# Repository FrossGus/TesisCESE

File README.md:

# TesisCESE
Tesis de la Carrera de Especialización en Sistemas Embebidos de la UBA

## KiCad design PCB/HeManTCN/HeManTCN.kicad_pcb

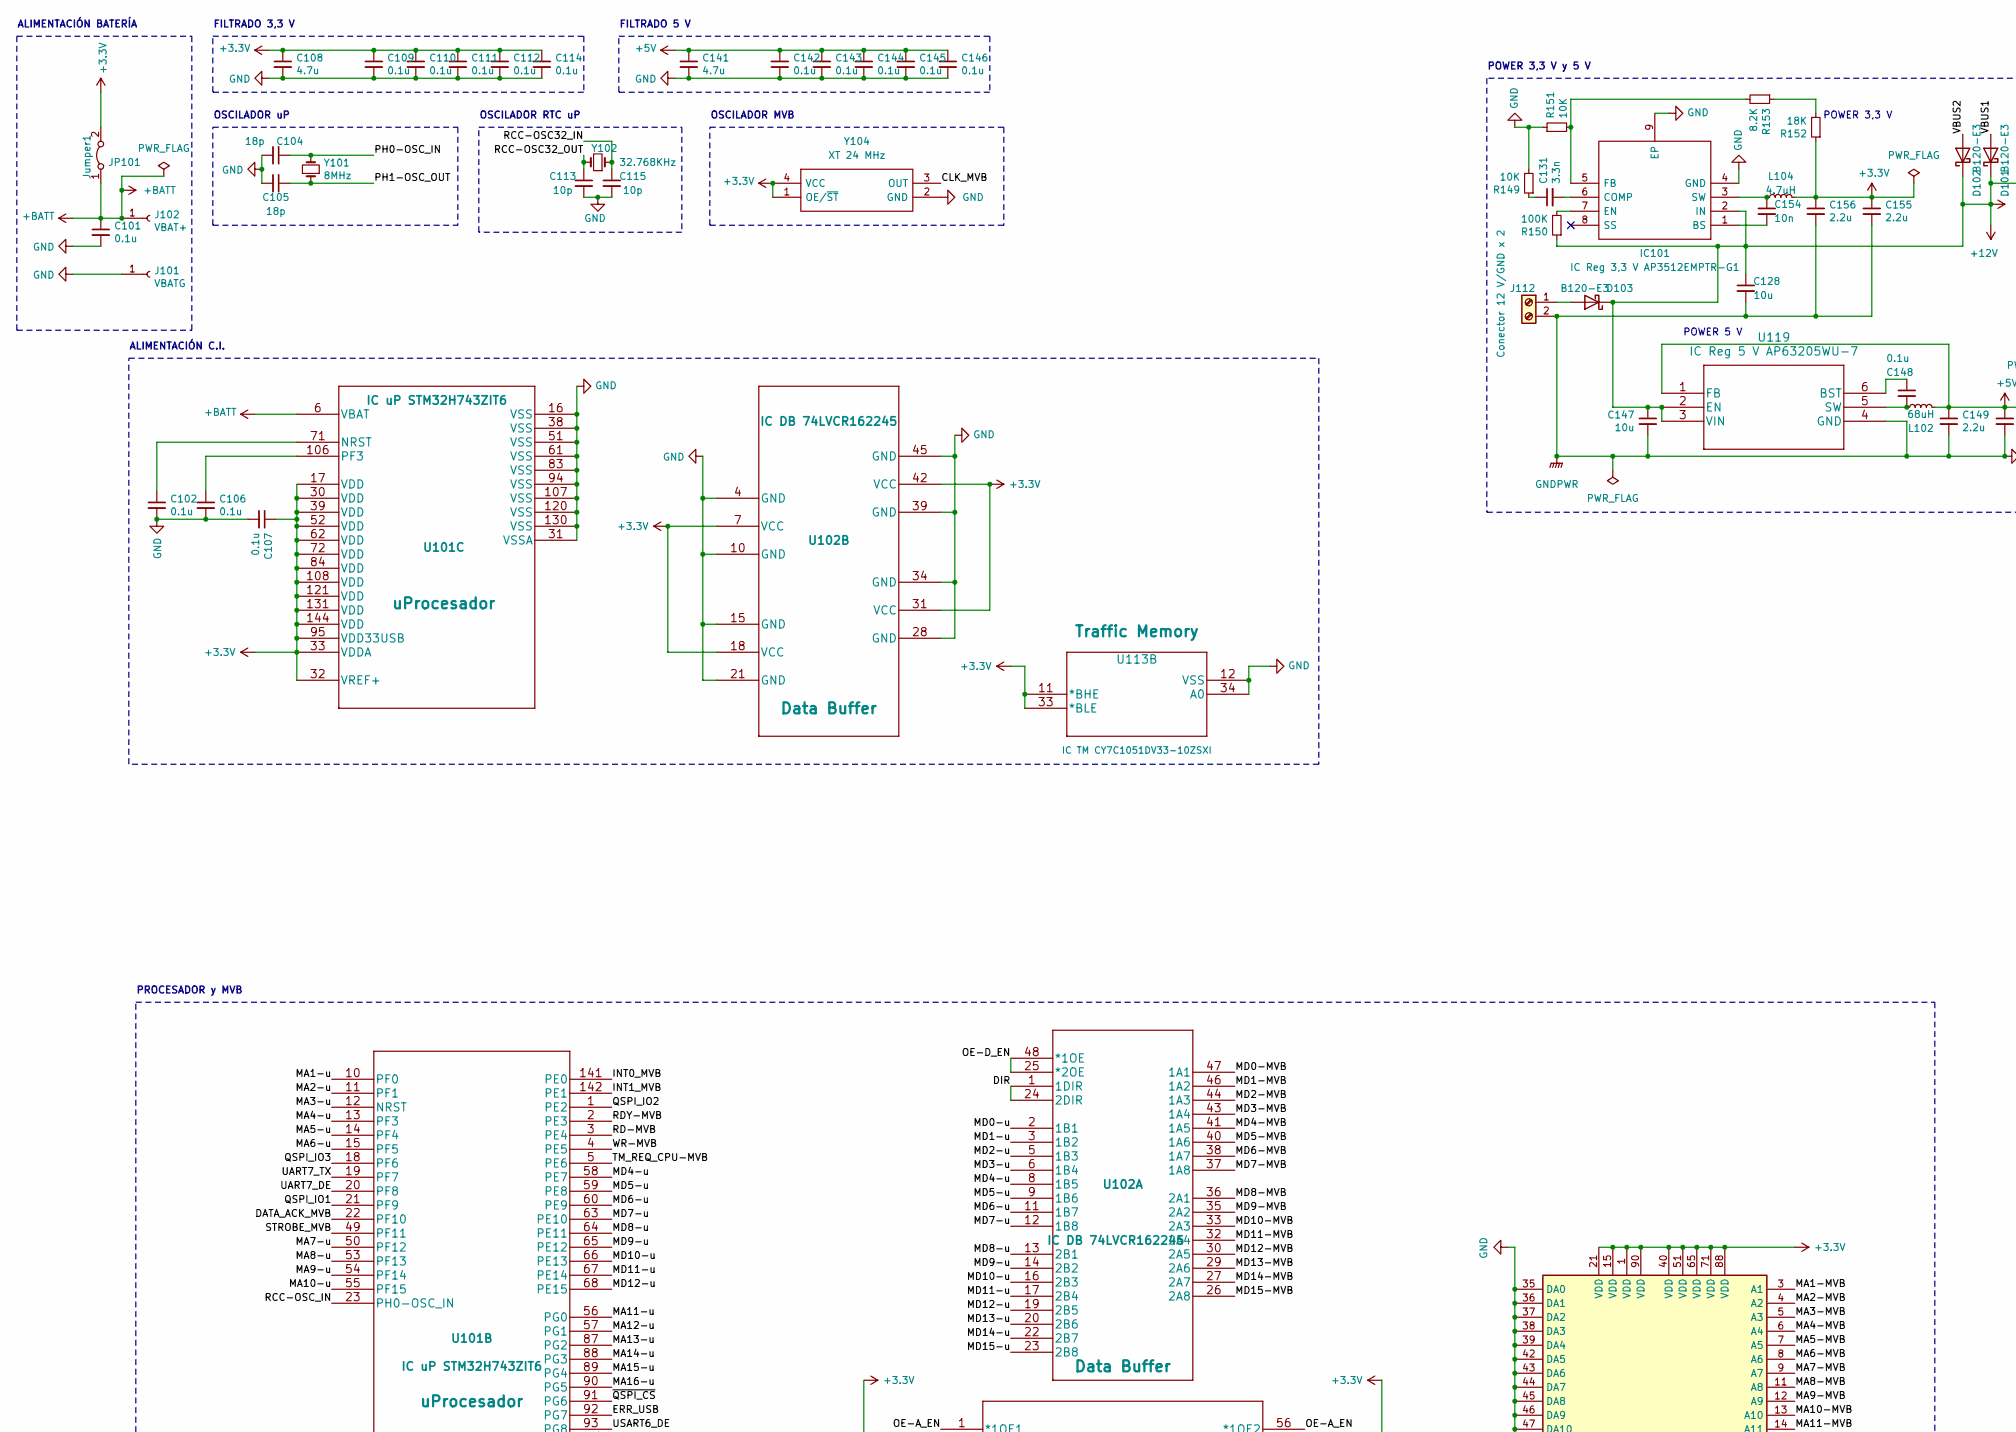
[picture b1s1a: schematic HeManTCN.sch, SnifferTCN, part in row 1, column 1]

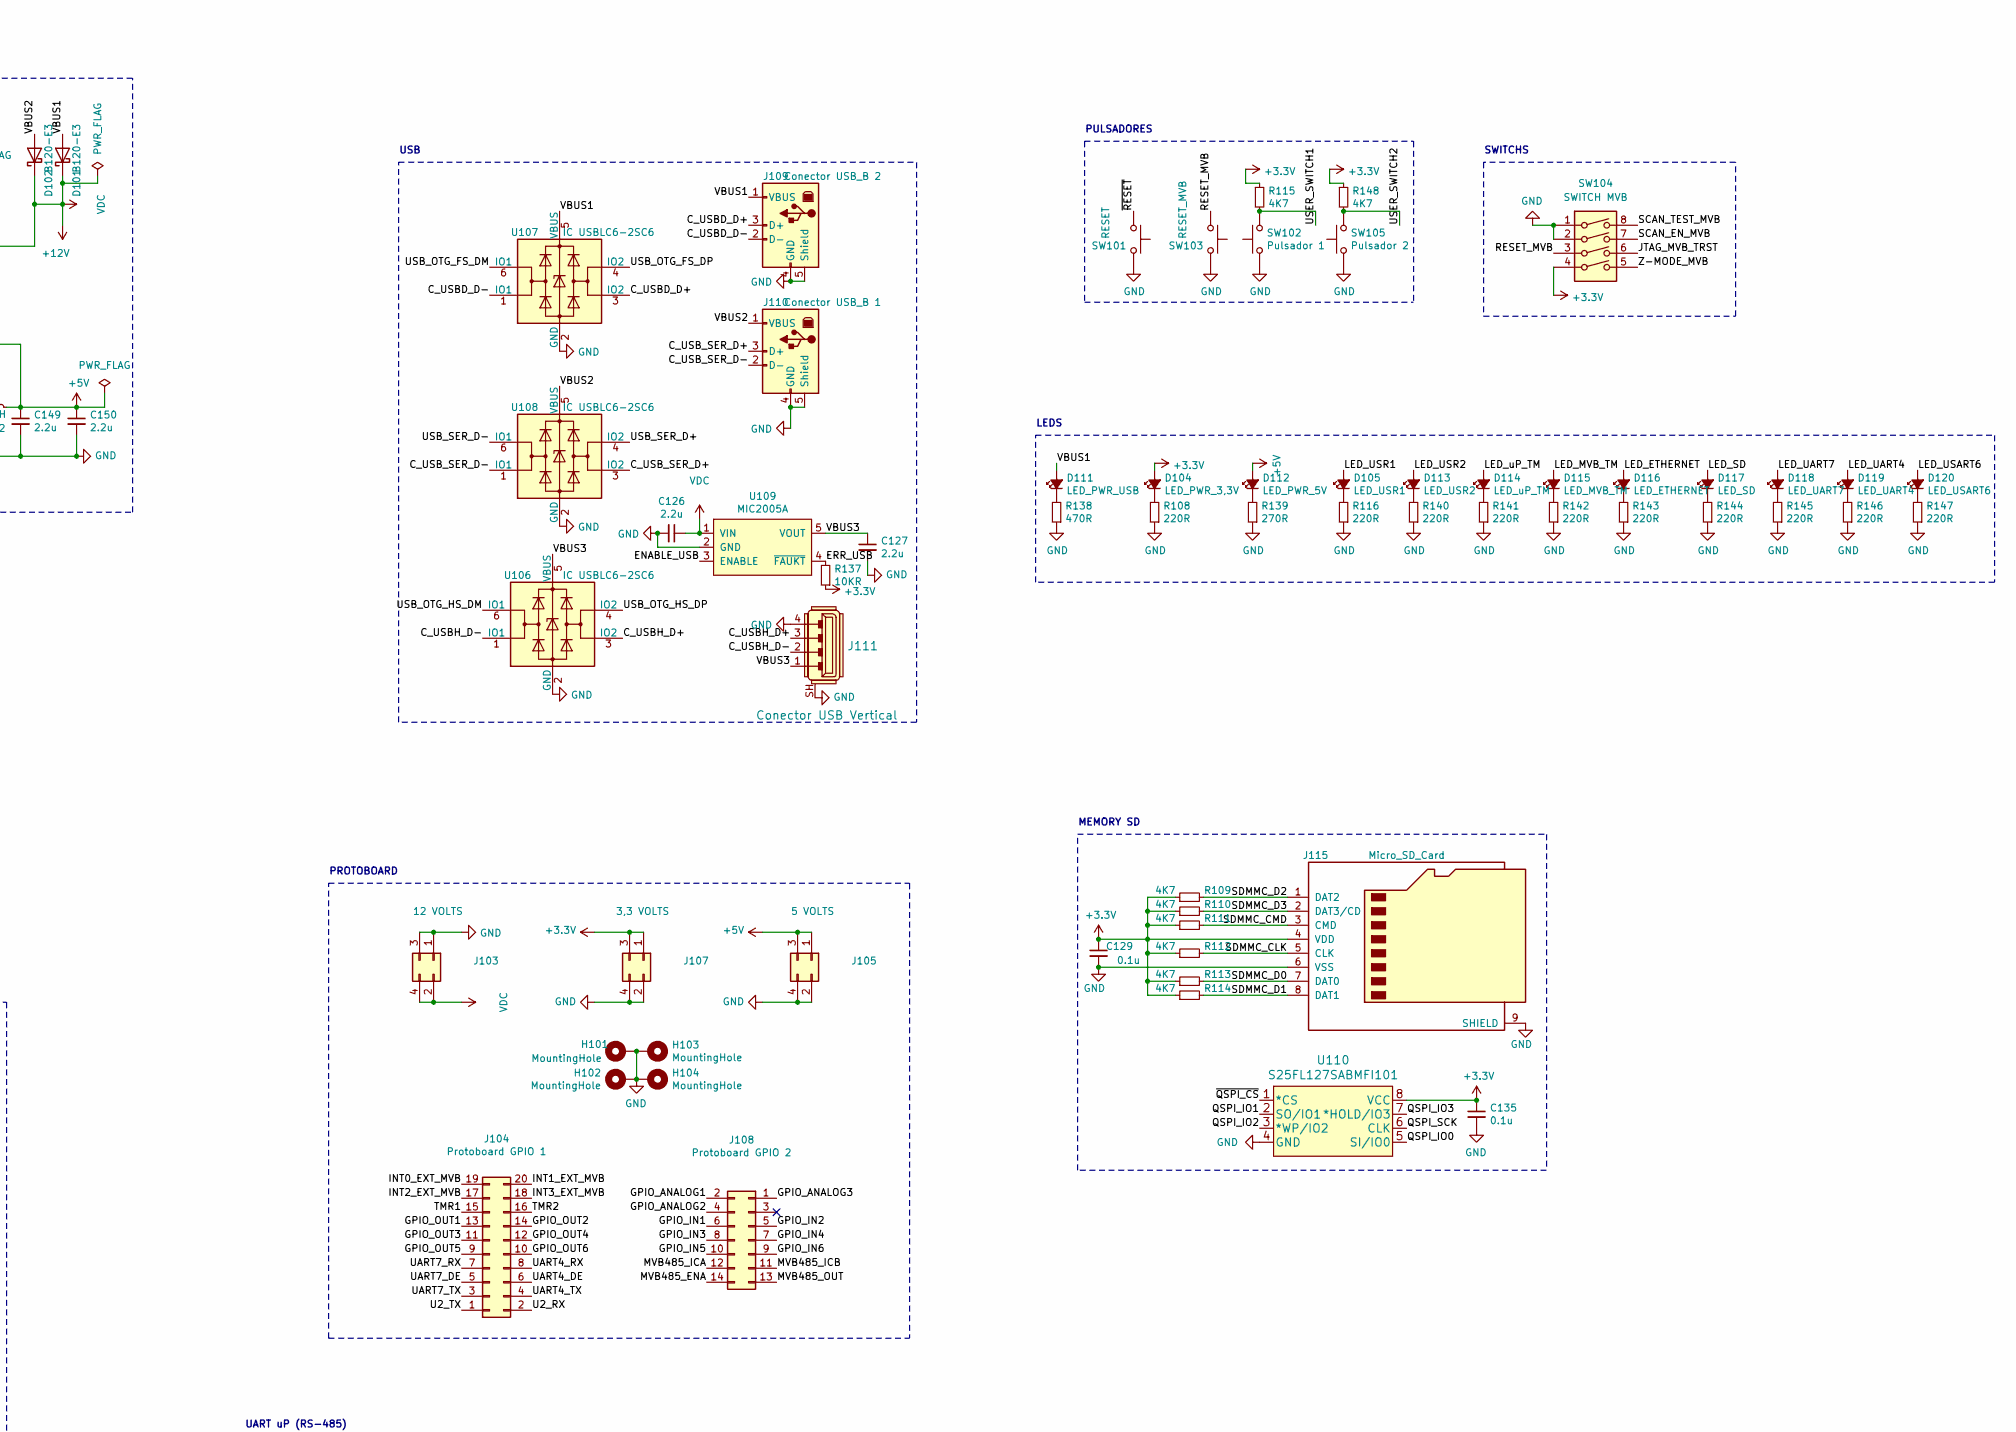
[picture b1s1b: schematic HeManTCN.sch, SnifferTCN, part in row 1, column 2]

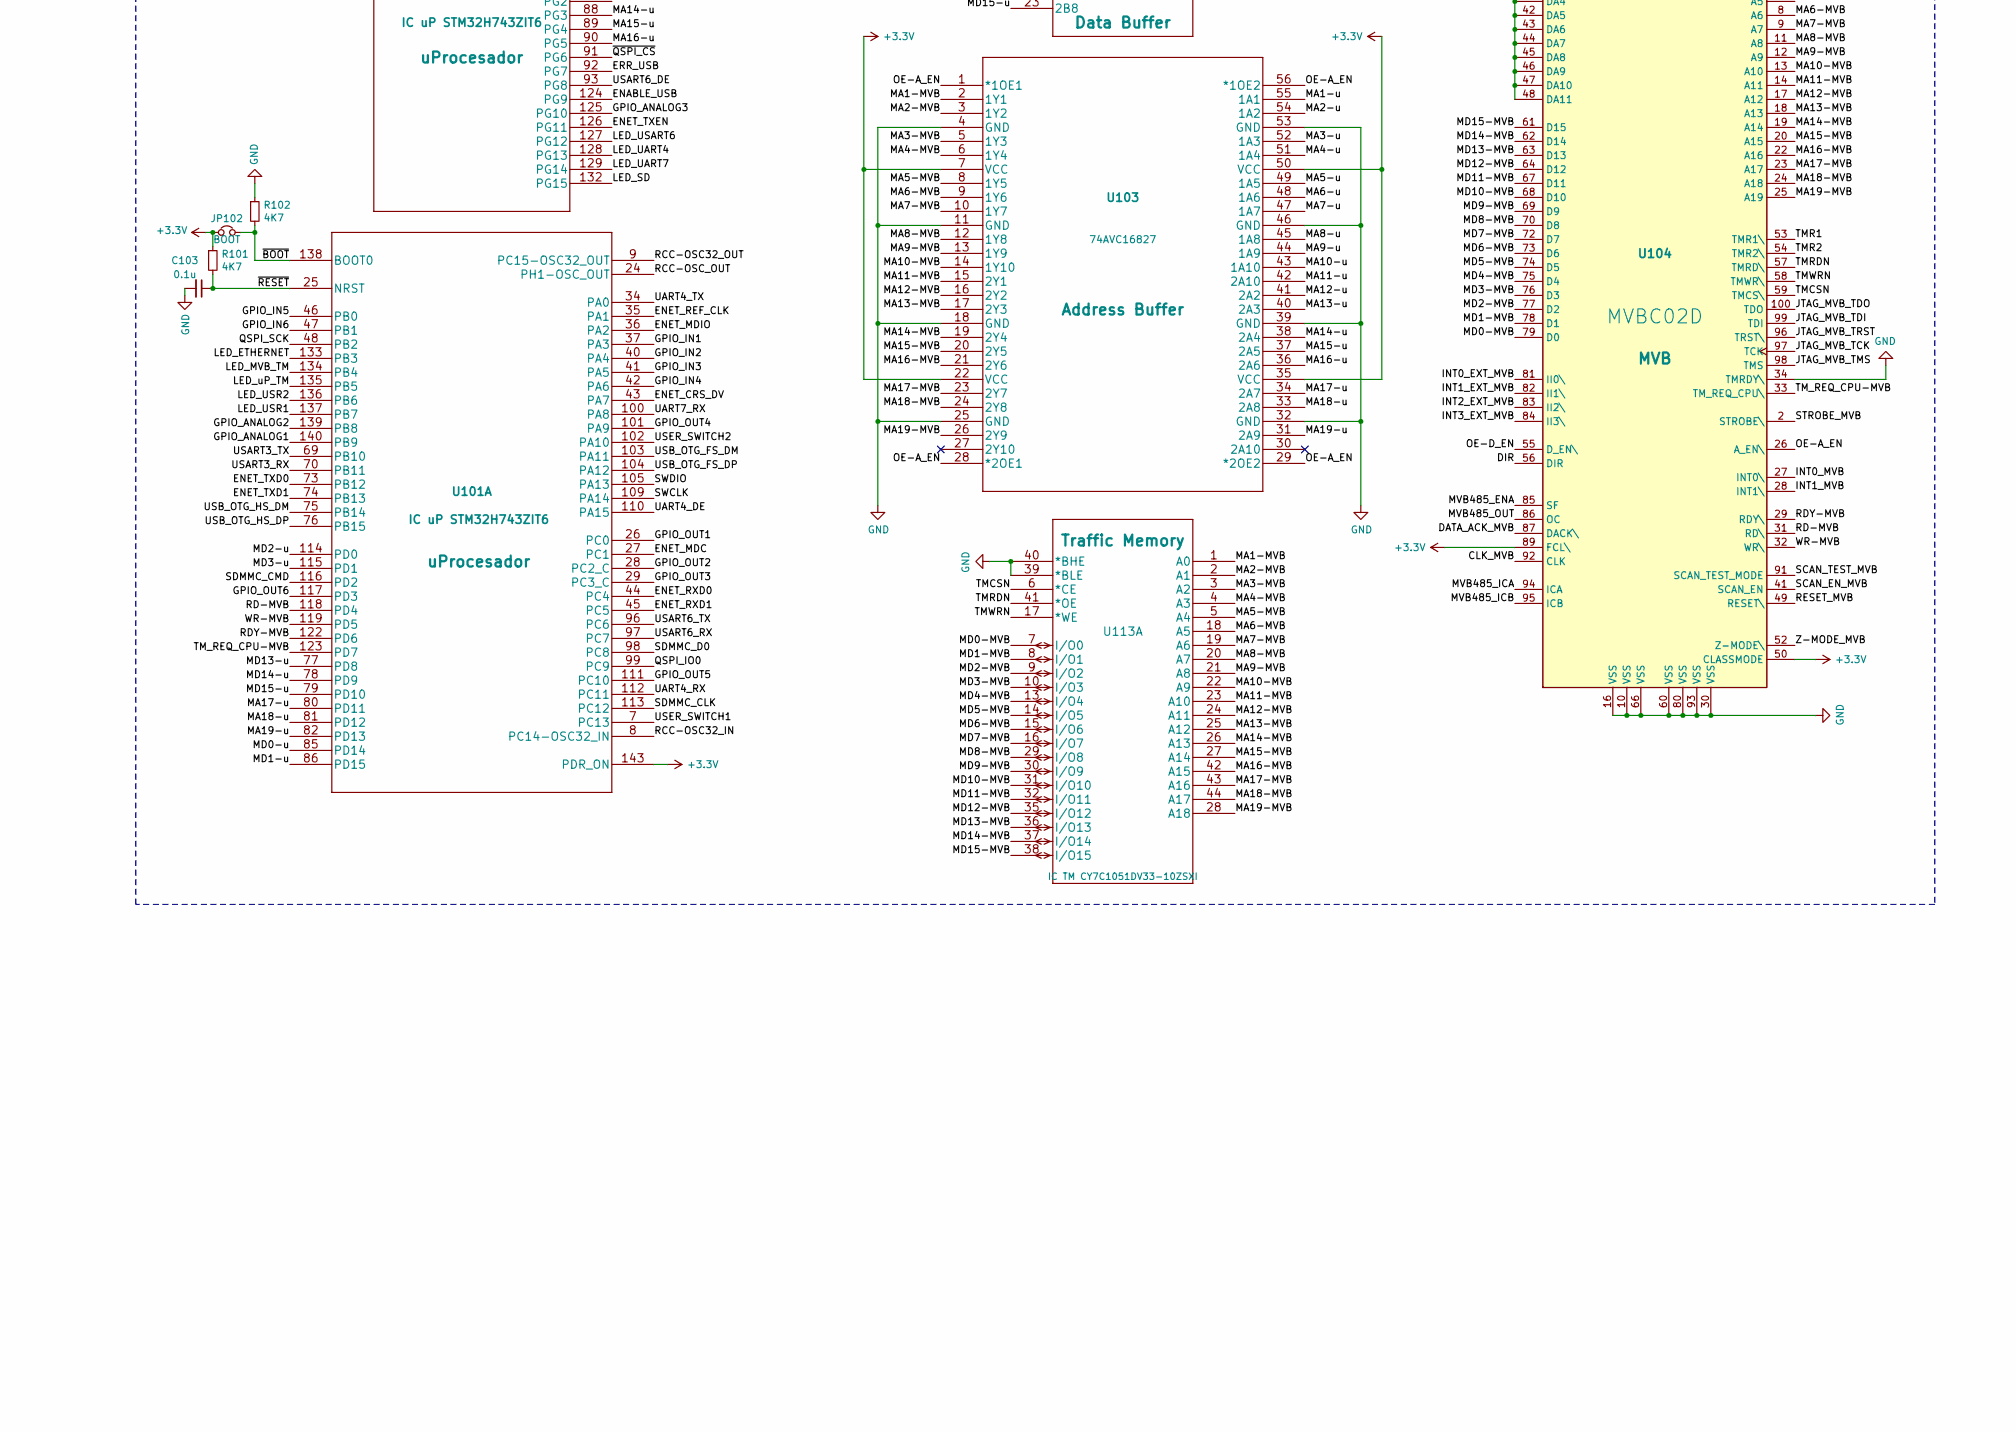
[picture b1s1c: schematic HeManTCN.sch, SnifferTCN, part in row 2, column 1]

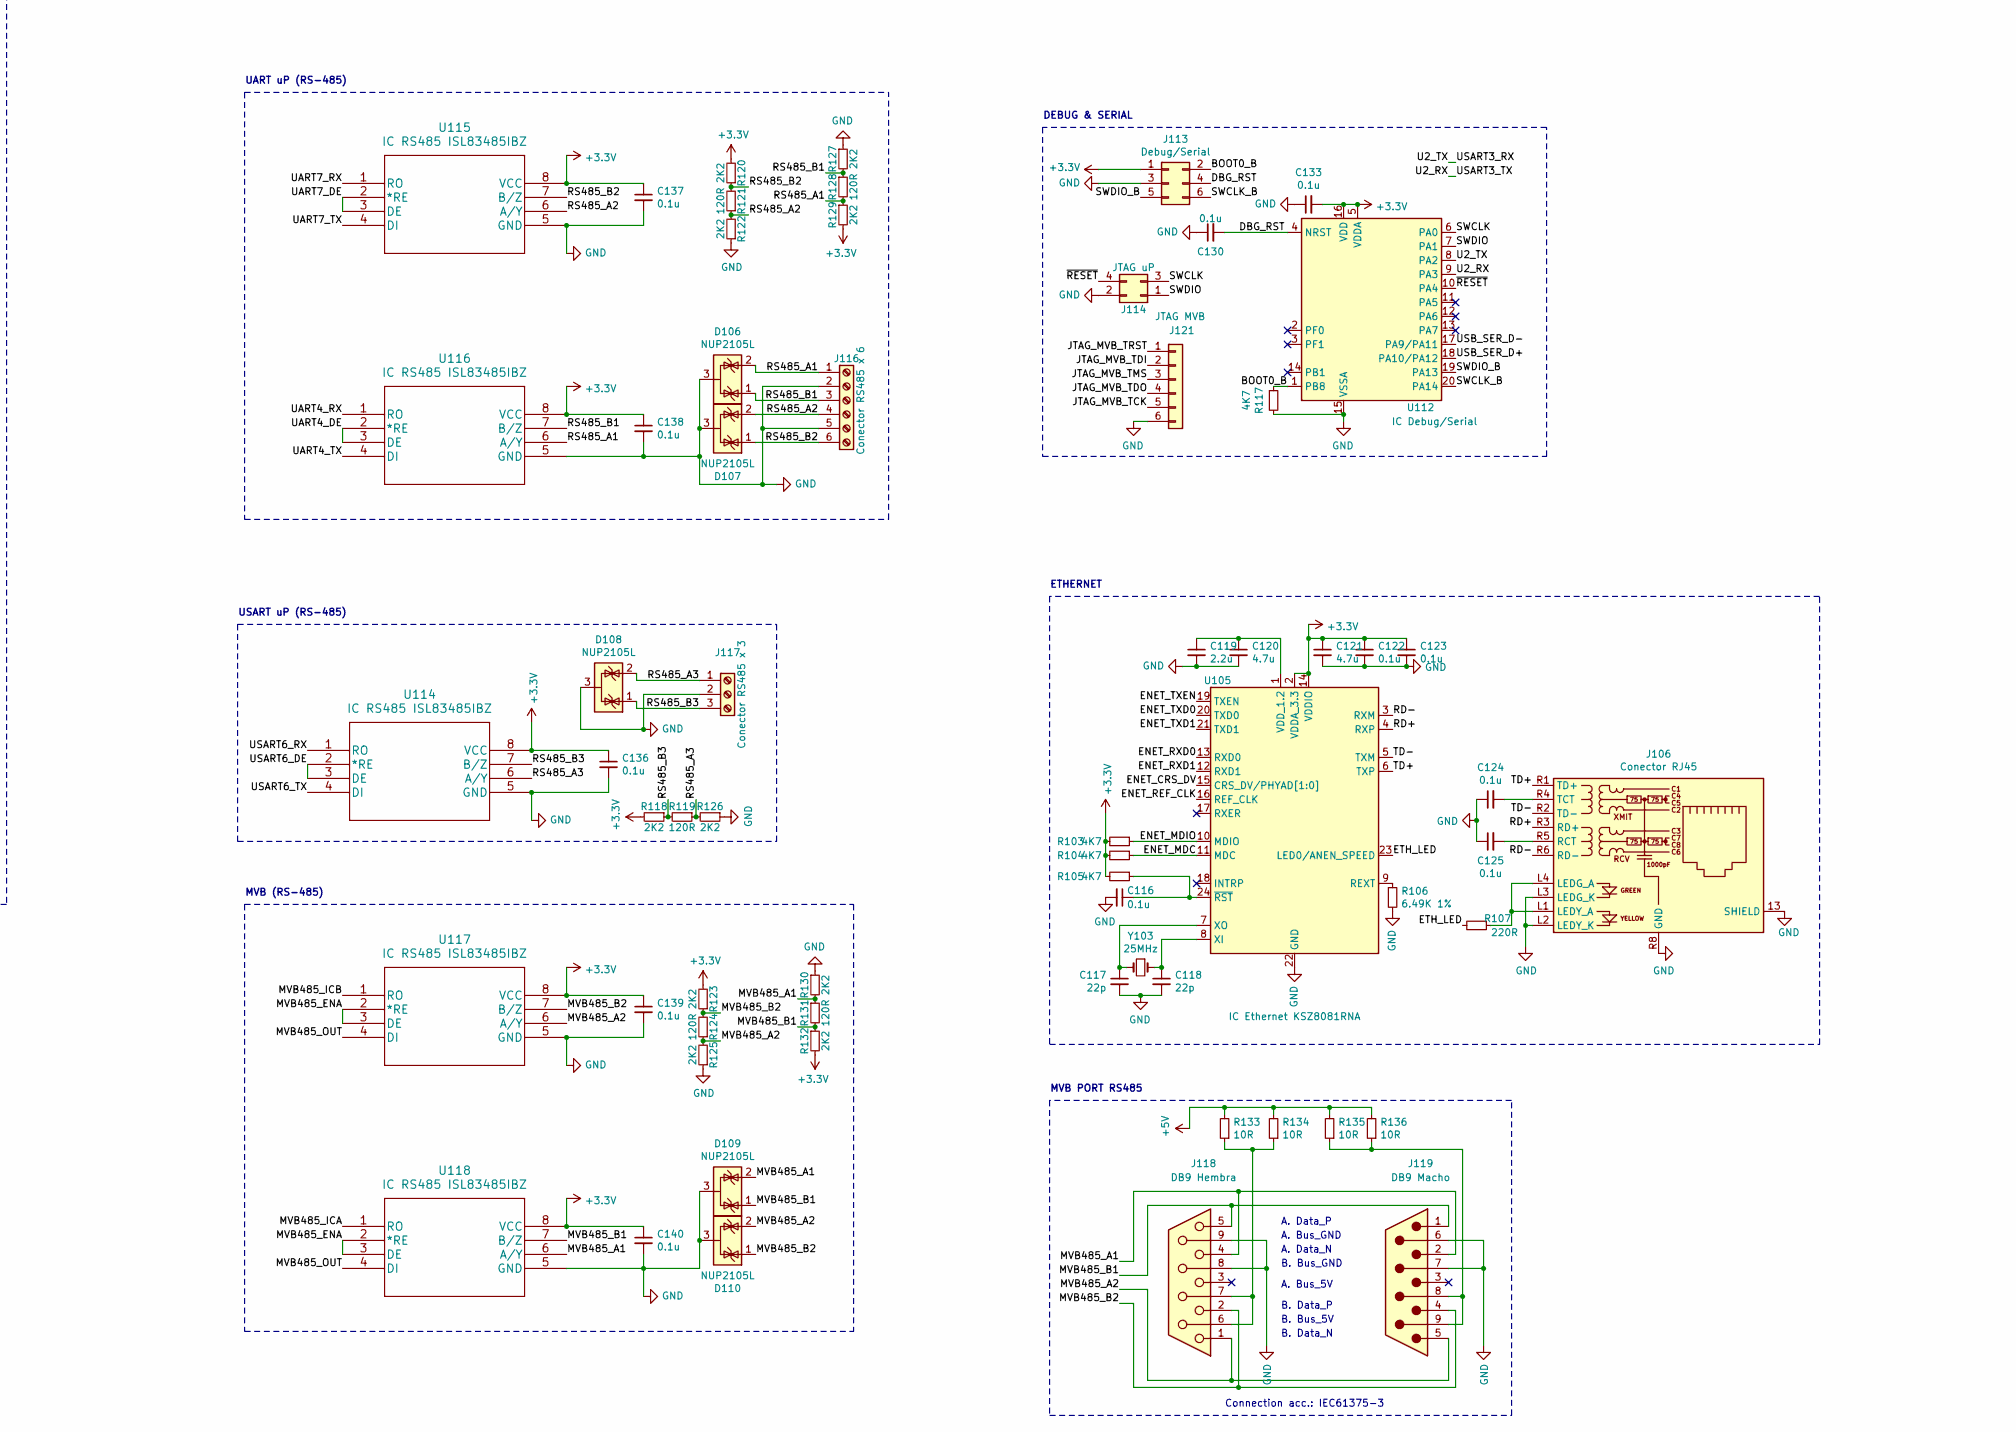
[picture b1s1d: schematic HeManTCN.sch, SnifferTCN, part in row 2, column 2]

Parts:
C101, C102, C103, C106, C107, C109, C110, C111, C112, C114, C116, C122, C123, C124, C125, C129, C130, C133, C135, C136, C137, C138, C139, C140, C142, C143, C144, C145, C146, C148: 0.1u; C_0805_2012Metric
C104, C105: 18p; C_0805_2012Metric
C108, C120, C121, C141: 4.7u; C_0805_2012Metric
C113, C115: 10p; C_0805_2012Metric
C117, C118: 22p; C_0805_2012Metric
C119, C126, C127, C149, C150, C155, C156: 2.2u; C_0805_2012Metric
C128, C147: 10u; C_0805_2012Metric
C131: 3.3n; C_0805_2012Metric
C154: 10n; C_0805_2012Metric
D101, D102, D103: B120-E3; D_SOD-123
D104: LED_PWR_3,3V; LED_0805_2012Metric_Castellated
D105: LED_USR1; LED_0805_2012Metric_Castellated
D106, D107, D108, D109, D110: NUP2105L; SOT-23
D111: LED_PWR_USB; LED_0805_2012Metric_Castellated
D112: LED_PWR_5V; LED_0805_2012Metric_Castellated
D113: LED_USR2; LED_0805_2012Metric_Castellated
D114: LED_uP_TM; LED_0805_2012Metric_Castellated
D115: LED_MVB_TM; LED_0805_2012Metric_Castellated
D116: LED_ETHERNET; LED_0805_2012Metric_Castellated
D117: LED_SD; LED_0805_2012Metric_Castellated
D118: LED_UART7; LED_0805_2012Metric_Castellated
D119: LED_UART4; LED_0805_2012Metric_Castellated
D120: LED_USART6; LED_0805_2012Metric_Castellated
H101, H102, H103, H104: MountingHole; MountingHole_3.2mm_M3_Pad_Via
IC101: IC Reg 3,3 V AP3512EMPTR-G1; AP3512EMPTR-G1; Mouser Part Number 621-AP3512EMPTR-G1
J101: VBATG; TestPoint_Loop_D1.80mm_Drill1.0mm_Beaded
J102: VBAT+; TestPoint_Loop_D1.80mm_Drill1.0mm_Beaded
J103: 12 VOLTS; PinSocket_2x05_P2.54mm_Vertical
J104: Protoboard GPIO 1; PinSocket_2x12_P2.54mm_Vertical
J105: 5 VOLTS; PinSocket_2x05_P2.54mm_Vertical
J106: Conector RJ45; RJ45_Amphenol_RJMG1BD3B8K1ANR
J107: 3,3 VOLTS; PinSocket_2x05_P2.54mm_Vertical
J108: Protoboard GPIO 2; PinSocket_2x12_P2.54mm_Vertical
J109: Conector USB_B 2; USB_B_OST_USB-B1HSxx_Horizontal
J110: Conector USB_B 1; USB_B_OST_USB-B1HSxx_Horizontal
J111: Conector USB Vertical; USB_A_Female_Vertical_RA_73725-0110BLF; MPN 73725-0110BLF; Digi-Key_PN 609-1041-ND
J112: Conector 12 V/GND x 2; Bornera2Pines_282837-2
J113: Debug/Serial; PinHeader_2x03_P2.54mm_Vertical
J114: JTAG uP; PinHeader_2x02_P2.54mm_Vertical
J115: Micro_SD_Card; microSD_HC_Hirose_DM3D-SF
J116: Conector RS485 x 6; Bornera6Pines_282837-6
J117: Conector RS485 x 3; Bornera3Pines_282837-3
J118: DB9 Hembra; DSUB-9_Female_Horizontal_P2.77x2.84mm_EdgePinOffset4.94mm_H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
J119: DB9 Macho; DSUB-9_Male_Horizontal_P2.77x2.84mm_EdgePinOffset4.94mm_Hou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
J121: JTAG MVB; PinSocket_2x05_P2.54mm_Vertical
JP101: Jumper1; PinHeader_1x02_P2.54mm_Vertical
JP102: BOOT; PinHeader_1x02_P2.54mm_Horizontal
L102: 68uH; L_6.3x6.3_H3
L104: 4.7uH; L_6.3x6.3_H3
R101, R102, R103, R104, R105, R109, R110, R111, R112, R113, R114, R115, R117, R148: 4K7; R_0805_2012Metric
R106: 6.49K 1%; R_0805_2012Metric
R107, R108, R116, R140, R141, R142, R143, R144, R145, R146, R147: 220R; R_0805_2012Metric
R118, R120, R122, R123, R125, R126, R127, R129, R130, R132: 2K2; R_0805_2012Metric
R119, R121, R124, R128, R131: 120R; R_0805_2012Metric
R133, R134, R135, R136: 10R; R_0805_2012Metric
R137: 10KR; R_0805_2012Metric
R138: 470R; R_0805_2012Metric
R139: 270R; R_0805_2012Metric
R149, R151: 10K; R_0805_2012Metric
R150: 100K; R_0805_2012Metric
R152: 18K; R_0805_2012Metric
R153: 8.2K; R_0805_2012Metric
SW101: RESET; Pulsador_TL3342F160QG
SW102: Pulsador 1; Pulsador_TL3342F160QG
SW103: RESET_MVB; Pulsador_TL3342F160QG
SW104: SWITCH MVB; Pulsador_TL3342F160QG
SW105: Pulsador 2; Pulsador_TL3342F160QG
U101: IC uP STM32H743ZIT6; LQFP-144_STM
U102: IC DB 74LVCR162245; DataBuffer SN74LVCR162245DGGR
U103: 74AVC16827; AddressBuffer SN74AVC16827DGVR
U104: MVBC02D; PQFP-100_14x20mm_P0.65mm
U105: IC Ethernet KSZ8081RNA; QFN-24-1EP_4x4mm_P0.5mm_EP2.6x2.6mm
U106, U107, U108: IC USBLC6-2SC6; SOT-23-6
U109: MIC2005A; SOT-23-5
U110: S25FL127SABMFI101
U112: IC Debug/Serial; TSSOP-20_4.4x6.5mm_P0.65mm
U113: IC TM CY7C1051DV33-10ZSXI; TSOP-44
U114, U115, U116, U117, U118: IC RS485 ISL83485IBZ; SOIC8_4X5_INR
U119: IC Reg 5 V AP63205WU-7; SOIC_05WU-7_DIO
Y101: 8MHz; Crystal_SMD_5032-2Pin_5.0x3.2mm
Y102: 32.768KHz; Crystal_SMD_MicroCrystal_CC7V-T1A-2Pin_3.2x1.5mm
Y103: 25MHz; Crystal_SMD_5032-2Pin_5.0x3.2mm
Y104: XT 24 MHz; SG7050CAN1000000MTJGA3; Mouser Part Number 732-7050CA24.0TJGA3

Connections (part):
+3V3: C107.1, C108.1, C109.1, C110.1, C111.1, C112.1, C114.1, C121.1, C122.1, C123.1, C129.1, C133.2, C135.1, C136.1, C137.1, C138.1, C139.1, C140.1, C155.1, C156.1, D104.2 (A), J107.1, J107.3, J113.1, J115.4 (VDD), JP101.2 (B), JP102.1, L104.2, R101.1, R103.2, R104.2, R105.2, R109.1, R110.1, R111.1, R112.1, R113.1, R114.1, R115.1, R118.2, R120.2, R123.2, R129.2, R132.2, R137.1, R148.1, R152.1, SW104.4, U101.17 (VDD), U101.30 (VDD), U101.32 (VREF+), U101.33 (VDDA), U101.39 (VDD), U101.52 (VDD), U101.62 (VDD), U101.72 (VDD), U101.84 (VDD), U101.95 (VDD33USB), U101.108 (VDD), U101.121 (VDD), U101.131 (VDD), U101.143 (PDR_ON), U101.144 (VDD), U102.7 (VCC), U102.18 (VCC), U102.31 (VCC), U102.42 (VCC), U103.7 (VCC), U103.22 (VCC), U103.35 (VCC), U103.50 (VCC), U104.1 (VDD), U104.15 (VDD), U104.21 (VDD), U104.40 (VDD), U104.50 (CLASSMODE), U104.51 (VDD), U104.65 (VDD), U104.71 (VDD), U104.88 (VDD), U104.89 (FCL\), U104.90 (VDD), U105.2 (VDDA_3.3), U105.14 (VDDIO), U110.8 (VCC), U112.5 (VDDA), U112.16 (VDD), U113.11 (*BHE), U113.33 (*BLE), U114.8 (VCC), U115.8 (VCC), U116.8 (VCC), U117.8 (VCC), U118.8 (VCC), Y104.1 (OE/~ST), Y104.4 (VCC)
+5V: C141.1, C142.1, C143.1, C144.1, C145.1, C146.1, C149.1, C150.1, D112.2 (A), J105.1, J105.3, L102.2, R133.2, R134.2, R135.2, R136.2, U119.1 (FB)
+12V: C126.1, C128.1, C147.1, D101.1 (K), D102.1 (K), D103.1 (K), IC101.2 (IN), J103.2, J103.4, R150.1, U109.1 (VIN), U119.2 (EN), U119.3 (VIN)
+BATT: C101.1, J102.1, JP101.1 (A), U101.6 (VBAT)
/BOOT0_B: J113.2, R117.1, U112.1 (PB8)
/CLK_MVB: U104.92 (CLK), Y104.3 (OUT)
/C_USBD_D+: J109.3 (D+), U107.3 (IO2)
/C_USBD_D-: J109.2 (D-), U107.1 (IO1)
/C_USBH_D+: J111.3, U106.3 (IO2)
/C_USBH_D-: J111.2, U106.1 (IO1)
/C_USB_SER_D+: J110.3 (D+), U108.3 (IO2)
/C_USB_SER_D-: J110.2 (D-), U108.1 (IO1)
/DATA_ACK_MVB: U101.22 (PF10), U104.87 (DACK\)
/DBG_RST: C130.2, J113.4, U112.4 (NRST)
/DIR: U102.1 (1DIR), U102.24 (2DIR), U104.56 (DIR)
/ENABLE_USB: U101.124 (PG9), U109.3 (ENABLE)
/ENET_CRS_DV: U101.43 (PA7), U105.15 (CRS_DV/PHYAD[1:0])
/ENET_MDC: R104.1, U101.27 (PC1), U105.11 (MDC)
/ENET_MDIO: R103.1, U101.36 (PA2), U105.10 (MDIO)
/ENET_REF_CLK: U101.35 (PA1), U105.16 (REF_CLK)
/ENET_RXD0: U101.44 (PC4), U105.13 (RXD0)
/ENET_RXD1: U101.45 (PC5), U105.12 (RXD1)
/ENET_TXD0: U101.73 (PB12), U105.20 (TXD0)
/ENET_TXD1: U101.74 (PB13), U105.21 (TXD1)
/ENET_TXEN: U101.126 (PG11), U105.19 (TXEN)
/ERR_USB: R137.2, U101.92 (PG7), U109.4 (~FAUKT)
/ETH_LED: R107.2, U105.23 (LED0/ANEN_SPEED)
/GPIO_ANALOG1: J108.2, U101.140 (PB9)
/GPIO_ANALOG2: J108.4, U101.139 (PB8)
/GPIO_ANALOG3: J108.1, U101.125 (PG10)
/GPIO_IN1: J108.6, U101.37 (PA3)
/GPIO_IN2: J108.5, U101.40 (PA4)
/GPIO_IN3: J108.8, U101.41 (PA5)
/GPIO_IN4: J108.7, U101.42 (PA6)
/GPIO_IN5: J108.10, U101.46 (PB0)
/GPIO_IN6: J108.9, U101.47 (PB1)
/GPIO_OUT1: J104.13, U101.26 (PC0)
/GPIO_OUT2: J104.14, U101.28 (PC2_C)
/GPIO_OUT3: J104.11, U101.29 (PC3_C)
/GPIO_OUT4: J104.12, U101.101 (PA9)
/GPIO_OUT5: J104.9, U101.111 (PC10)
/GPIO_OUT6: J104.10, U101.117 (PD3)
/INT0_EXT_MVB: J104.19, U104.81 (II0\)
/INT0_MVB: U101.141 (PE0), U104.27 (INT0\)
/INT1_EXT_MVB: J104.20, U104.82 (II1\)
/INT1_MVB: U101.142 (PE1), U104.28 (INT1\)
/INT2_EXT_MVB: J104.17, U104.83 (II2\)
/INT3_EXT_MVB: J104.18, U104.84 (II3\)
/JTAG_MVB_TCK: J121.5, U104.97 (TCK)
/JTAG_MVB_TDI: J121.2, U104.99 (TDI)
/JTAG_MVB_TDO: J121.4, U104.100 (TDO)
/JTAG_MVB_TMS: J121.3, U104.98 (TMS)
/JTAG_MVB_TRST: J121.1, SW104.6, U104.96 (TRST\)
/LED_ETHERNET: D116.2 (A), U101.133 (PB3)
/LED_MVB_TM: D115.2 (A), U101.134 (PB4)
/LED_SD: D117.2 (A), U101.132 (PG15)
/LED_UART4: D119.2 (A), U101.128 (PG13)
/LED_UART7: D118.2 (A), U101.129 (PG14)
/LED_USART6: D120.2 (A), U101.127 (PG12)
/LED_USR1: D105.2 (A), U101.137 (PB7)
/LED_USR2: D113.2 (A), U101.136 (PB6)
/LED_uP_TM: D114.2 (A), U101.135 (PB5)
/MA1-MVB: U103.2 (1Y1), U104.3 (A1), U113.1 (A0)
/MA1-u: U101.10 (PF0), U103.55 (1A1)
/MA2-MVB: U103.3 (1Y2), U104.4 (A2), U113.2 (A1)
/MA2-u: U101.11 (PF1), U103.54 (1A2)
/MA3-MVB: U103.5 (1Y3), U104.5 (A3), U113.3 (A2)
/MA3-u: U101.12 (NRST), U103.52 (1A3)
/MA4-MVB: U103.6 (1Y4), U104.6 (A4), U113.4 (A3)
/MA4-u: U101.13 (PF3), U103.51 (1A4)
/MA5-MVB: U103.8 (1Y5), U104.7 (A5), U113.5 (A4)
/MA5-u: U101.14 (PF4), U103.49 (1A5)
/MA6-MVB: U103.9 (1Y6), U104.8 (A6), U113.18 (A5)
/MA6-u: U101.15 (PF5), U103.48 (1A6)
/MA7-MVB: U103.10 (1Y7), U104.9 (A7), U113.19 (A6)
/MA7-u: U101.50 (PF12), U103.47 (1A7)
/MA8-MVB: U103.12 (1Y8), U104.11 (A8), U113.20 (A7)
/MA8-u: U101.53 (PF13), U103.45 (1A8)
/MA9-MVB: U103.13 (1Y9), U104.12 (A9), U113.21 (A8)
/MA9-u: U101.54 (PF14), U103.44 (1A9)
/MA10-MVB: U103.14 (1Y10), U104.13 (A10), U113.22 (A9)
/MA10-u: U101.55 (PF15), U103.43 (1A10)
/MA11-MVB: U103.15 (2Y1), U104.14 (A11), U113.23 (A10)
/MA11-u: U101.56 (PG0), U103.42 (2A10)
/MA12-MVB: U103.16 (2Y2), U104.17 (A12), U113.24 (A11)
/MA12-u: U101.57 (PG1), U103.41 (2A2)
/MA13-MVB: U103.17 (2Y3), U104.18 (A13), U113.25 (A12)
/MA13-u: U101.87 (PG2), U103.40 (2A3)
/MA14-MVB: U103.19 (2Y4), U104.19 (A14), U113.26 (A13)
/MA14-u: U101.88 (PG3), U103.38 (2A4)
/MA15-MVB: U103.20 (2Y5), U104.20 (A15), U113.27 (A14)
/MA15-u: U101.89 (PG4), U103.37 (2A5)
/MA16-MVB: U103.21 (2Y6), U104.22 (A16), U113.42 (A15)
/MA16-u: U101.90 (PG5), U103.36 (2A6)
/MA17-MVB: U103.23 (2Y7), U104.23 (A17), U113.43 (A16)
/MA17-u: U101.80 (PD11), U103.34 (2A7)
/MA18-MVB: U103.24 (2Y8), U104.24 (A18), U113.44 (A17)
/MA18-u: U101.81 (PD12), U103.33 (2A8)
/MA19-MVB: U103.26 (2Y9), U104.25 (A19), U113.28 (A18)
/MA19-u: U101.82 (PD13), U103.31 (2A9)
/MD0-MVB: U102.47 (1A1), U104.79 (D0), U113.7 (I/O0)
/MD0-u: U101.85 (PD14), U102.2 (1B1)
/MD1-MVB: U102.46 (1A2), U104.78 (D1), U113.8 (I/O1)
/MD1-u: U101.86 (PD15), U102.3 (1B2)
/MD2-MVB: U102.44 (1A3), U104.77 (D2), U113.9 (I/O2)
/MD2-u: U101.114 (PD0), U102.5 (1B3)
/MD3-MVB: U102.43 (1A4), U104.76 (D3), U113.10 (I/O3)
/MD3-u: U101.115 (PD1), U102.6 (1B4)
/MD4-MVB: U102.41 (1A5), U104.75 (D4), U113.13 (I/O4)
/MD4-u: U101.58 (PE7), U102.8 (1B5)
/MD5-MVB: U102.40 (1A6), U104.74 (D5), U113.14 (I/O5)
/MD5-u: U101.59 (PE8), U102.9 (1B6)
/MD6-MVB: U102.38 (1A7), U104.73 (D6), U113.15 (I/O6)
/MD6-u: U101.60 (PE9), U102.11 (1B7)
/MD7-MVB: U102.37 (1A8), U104.72 (D7), U113.16 (I/O7)
/MD7-u: U101.63 (PE10), U102.12 (1B8)
/MD8-MVB: U102.36 (2A1), U104.70 (D8), U113.29 (I/O8)
/MD8-u: U101.64 (PE11), U102.13 (2B1)
/MD9-MVB: U102.35 (2A2), U104.69 (D9), U113.30 (I/O9)
/MD9-u: U101.65 (PE12), U102.14 (2B2)
/MD10-MVB: U102.33 (2A3), U104.68 (D10), U113.31 (I/O10)
/MD10-u: U101.66 (PE13), U102.16 (2B3)
/MD11-MVB: U102.32 (2A4), U104.67 (D11), U113.32 (I/O11)
/MD11-u: U101.67 (PE14), U102.17 (2B4)
/MD12-MVB: U102.30 (2A5), U104.64 (D12), U113.35 (I/O12)
/MD12-u: U101.68 (PE15), U102.19 (2B5)
/MD13-MVB: U102.29 (2A6), U104.63 (D13), U113.36 (I/O13)
/MD13-u: U101.77 (PD8), U102.20 (2B6)
/MD14-MVB: U102.27 (2A7), U104.62 (D14), U113.37 (I/O14)
/MD14-u: U101.78 (PD9), U102.22 (2B7)
/MD15-MVB: U102.26 (2A8), U104.61 (D15), U113.38 (I/O15)
/MD15-u: U101.79 (PD10), U102.23 (2B8)
/MVB485_A1: D109.2 (K), J118.4, J119.2, R130.2, R131.1, U118.6 (A/Y)
/MVB485_A2: D110.2 (K), J118.1, J119.5, R124.1, R125.2, U117.6 (A/Y)
/MVB485_B1: D109.1 (K), J118.5, J119.1, R131.2, R132.1, U118.7 (B/Z)
/MVB485_B2: D110.1 (K), J118.2, J119.4, R123.1, R124.2, U117.7 (B/Z)
/MVB485_ENA: J108.14, U104.85 (SF), U117.2 (*RE), U117.3 (DE), U118.2 (*RE), U118.3 (DE)
/MVB485_ICA: J108.12, U104.94 (ICA), U118.1 (RO)
/MVB485_ICB: J108.11, U104.95 (ICB), U117.1 (RO)
/MVB485_OUT: J108.13, U104.86 (OC), U117.4 (DI), U118.4 (DI)
/OE-A_EN: U103.1 (*1OE1), U103.28 (*2OE1), U103.29 (*2OE2), U103.56 (*1OE2), U104.26 (A_EN\)
/OE-D_EN: U102.25 (*2OE), U102.48 (*1OE), U104.55 (D_EN\)
/PC14-OSC32_IN: C115.1, U101.8 (PC14-OSC32_IN), Y102.1
/PC15-OSC32_OUT: C113.1, U101.9 (PC15-OSC32_OUT), Y102.2
/PH0-OSC_IN: C104.1, Y101.2
/PH1-OSC_OUT: C105.1, Y101.1
/RD+: J106.R3 (RD+), U105.4 (RXP)
/RD-: J106.R6 (RD-), U105.3 (RXM)
/RD-MVB: U101.3 (PE4), U101.118 (PD4), U104.31 (RD\)
/RDY-MVB: U101.2 (PE3), U101.122 (PD6), U104.29 (RDY\)
/RESET_MVB: SW103.1, SW104.3, U104.49 (RESET\)
/RS485_A1: D106.2 (K), J116.1, R128.2, R129.1, U116.6 (A/Y)
/RS485_A2: D107.2 (K), J116.4, R121.1, R122.2, U115.6 (A/Y)
/RS485_A3: D108.2 (K), J117.1, R119.1, R126.2, U114.6 (A/Y)
/RS485_B1: D106.1 (K), J116.3, R127.2, R128.1, U116.7 (B/Z)
/RS485_B2: D107.1 (K), J116.6, R120.1, R121.2, U115.7 (B/Z)
/RS485_B3: D108.1 (K), J117.3, R118.1, R119.2, U114.7 (B/Z)
/SCAN_EN_MVB: SW104.7, U104.41 (SCAN_EN)
/SCAN_TEST_MVB: SW104.8, U104.91 (SCAN_TEST_MODE)
/SDMMC_CLK: J115.5 (CLK), R112.2, U101.113 (PC12)
/SDMMC_CMD: J115.3 (CMD), R111.2, U101.116 (PD2)
/SDMMC_D0: J115.7 (DAT0), R113.2, U101.98 (PC8)
/SDMMC_D1: J115.8 (DAT1), R114.2
/SDMMC_D2: J115.1 (DAT2), R109.2
/SDMMC_D3: J115.2 (DAT3/CD), R110.2
/STROBE_MVB: U101.49 (PF11), U104.2 (STROBE\)
/SWCLK: J114.3, U101.109 (PA14), U112.6 (PA0)
/SWCLK_B: J113.6, U112.20 (PA14)
/SWDIO: J114.1, U101.105 (PA13), U112.7 (PA1)
/SWDIO_B: J113.5, U112.19 (PA13)
/TD+: J106.R1 (TD+), U105.6 (TXP)
/TD-: J106.R2 (TD-), U105.5 (TXM)
/TMCSN: U104.59 (TMCS\), U113.6 (*CE)
/TMR1: J104.15, U104.53 (TMR1\)
/TMR2: J104.16, U104.54 (TMR2\)
/TMRDN: U104.57 (TMRD\), U113.41 (*OE)
/TMWRN: U104.58 (TMWR\), U113.17 (*WE)
/TM_REQ_CPU-MVB: U101.5 (PE6), U101.123 (PD7), U104.33 (TM_REQ_CPU\)
/U2_RX: J104.2, U101.69 (PB10), U112.9 (PA3)
/U2_TX: J104.1, U101.70 (PB11), U112.8 (PA2)
/UART4_DE: J104.6, U101.110 (PA15), U116.2 (*RE), U116.3 (DE)
/UART4_RX: J104.8, U101.112 (PC11), U116.1 (RO)
/UART4_TX: J104.4, U101.34 (PA0), U116.4 (DI)
/UART7_DE: J104.5, U101.20 (PF8), U115.2 (*RE), U115.3 (DE)
/UART7_RX: J104.7, U101.100 (PA8), U115.1 (RO)
/UART7_TX: J104.3, U101.19 (PF7), U115.4 (DI)
/USB_OTG_FS_DM: U101.103 (PA11), U107.6 (IO1)
/USB_OTG_FS_DP: U101.104 (PA12), U107.4 (IO2)
/USB_OTG_HS_DM: U101.75 (PB14), U106.6 (IO1)
/USB_OTG_HS_DP: U101.76 (PB15), U106.4 (IO2)
/USB_SER_D+: U108.4 (IO2), U112.18 (PA10/PA12)
/USB_SER_D-: U108.6 (IO1), U112.17 (PA9/PA11)
/USER_SWITCH1: R115.2, SW102.2, U101.7 (PC13)
/USER_SWITCH2: R148.2, SW105.2, U101.102 (PA10)
/VBUS1: D101.2 (A), D111.2 (A), J109.1 (VBUS), U107.5 (VBUS)
/VBUS2: D102.2 (A), J110.1 (VBUS), U108.5 (VBUS)
/VBUS3: C127.1, J111.1, U106.5 (VBUS), U109.5 (VOUT)
/WR-MVB: U101.4 (PE5), U101.119 (PD5), U104.32 (WR\)
/Z-MODE_MVB: SW104.5, U104.52 (Z-MODE\)
/~BOOT: JP102.2, R102.2, U101.138 (BOOT0)
/~RESET: C103.1, J114.4, R101.2, SW101.1, U101.25 (NRST), U112.10 (PA4)
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
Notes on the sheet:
MEMORY SD
DEBUG & SERIAL
USB
POWER 3,3 V
PROTOBOARD
OSCILADOR uP
ALIMENTACIÓN BATERÍA
FILTRADO 3,3 V
OSCILADOR RTC uP
ALIMENTACIÓN C.I.
POWER 3,3 V y 5 V
UART uP (RS-485)
ETHERNET
USART uP (RS-485)
MVB (RS-485)
A. Data_P
A. Bus_GND
A. Data_N
B. Bus_GND
A. Bus_5V
B. Data_P
B. Bus_5V
B. Data_N
Connection acc.: IEC61375-3
MVB PORT RS485
FILTRADO 5 V
POWER 5 V
SWITCHS
LEDS
OSCILADOR MVB
PROCESADOR y MVB
PULSADORES

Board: 2 copper layers, 171 parts (0 on the bottom side), 142 nets, no tracks yet.

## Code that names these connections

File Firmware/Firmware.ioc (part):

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Mcu.Name=STM32H743ZITx
Mcu.Package=LQFP144
Mcu.UserName=STM32H743ZITx
PA0.Mode=Asynchronous
PA0.Signal=UART4_TX
PA1.Mode=RMII
PA1.Signal=ETH_REF_CLK
PA10.GPIOParameters=GPIO_Label
PA10.GPIO_Label=USER_SWITCH2
PA10.Signal=GPIO_Input
PA11.Mode=Device_Only
PA11.Signal=USB_OTG_FS_DM
PA12.Mode=Device_Only
PA12.Signal=USB_OTG_FS_DP
PA13\ (JTMS/SWDIO).Mode=Serial_Wire
PA13\ (JTMS/SWDIO).Signal=DEBUG_JTMS-SWDIO
PA14\ (JTCK/SWCLK).Mode=Serial_Wire
PA14\ (JTCK/SWCLK).Signal=DEBUG_JTCK-SWCLK
PA15\ (JTDI).Mode=Hardware Flow Control (RS485)
PA15\ (JTDI).Signal=UART4_DE
PA2.Mode=RMII
PA2.Signal=ETH_MDIO
PA3.GPIOParameters=GPIO_Label
PA3.GPIO_Label=GPIO_IN1
PA3.Signal=GPIO_Input
PA4.GPIOParameters=GPIO_Label
PA4.GPIO_Label=GPIO_IN2
PA4.Signal=GPIO_Input
PA5.GPIOParameters=GPIO_Label
PA5.GPIO_Label=GPIO_IN3
PA5.Signal=GPIO_Input
PA6.GPIOParameters=GPIO_Label
PA6.GPIO_Label=GPIO_IN4
PA6.Signal=GPIO_Input
PA7.Mode=RMII
PA7.Signal=ETH_CRS_DV
PA8.Mode=Asynchronous
PA8.Signal=UART7_RX
PA9.GPIOParameters=GPIO_Label
PA9.GPIO_Label=GPIO_OUT4
PA9.Signal=GPIO_Output
PB0.GPIOParameters=GPIO_Label
PB0.GPIO_Label=GPIO_IN5
PB0.Signal=GPIO_Input
PB1.GPIOParameters=GPIO_Label
PB1.GPIO_Label=GPIO_IN6
PB1.Signal=GPIO_Input
PB10.Mode=Asynchronous
PB10.Signal=USART3_TX
PB11.Mode=Asynchronous
PB11.Signal=USART3_RX
PB12.Mode=RMII
PB12.Signal=ETH_TXD0
PB13.Mode=RMII
PB13.Signal=ETH_TXD1
PB14.Mode=Host_FS
PB14.Signal=USB_OTG_HS_DM
PB15.Mode=Host_FS
PB15.Signal=USB_OTG_HS_DP
PB2.GPIOParameters=GPIO_Label
PB2.GPIO_Label=QSPI_SCK
PB2.Mode=Single Bank 1
PB2.Signal=QUADSPI_CLK
PB3\ (JTDO/TRACESWO).GPIOParameters=GPIO_Label
PB3\ (JTDO/TRACESWO).GPIO_Label=LED_ETHERNET
PB3\ (JTDO/TRACESWO).Signal=GPIO_Output
PB4\ (NJTRST).GPIOParameters=GPIO_Label
PB4\ (NJTRST).GPIO_Label=LED_MVB_TM
PB4\ (NJTRST).Signal=GPIO_Output
PB5.GPIOParameters=GPIO_Label
PB5.GPIO_Label=LED_uP_TM
PB5.Signal=GPIO_Output
PB6.GPIOParameters=GPIO_Label
PB6.GPIO_Label=LED_USR2
PB6.Signal=GPIO_Output
PB7.GPIOParameters=GPIO_Label
PB7.GPIO_Label=LED_USR1
PB7.Signal=GPIO_Output
PB8.GPIOParameters=GPIO_Label
PB8.GPIO_Label=GPIO_ANALOG2
PB8.Signal=GPIO_Analog
PB9.GPIOParameters=GPIO_Label
PB9.GPIO_Label=GPIO_ANALOG1
PB9.Signal=GPIO_Analog
PC0.GPIOParameters=GPIO_Label
PC0.GPIO_Label=GPIO_OUT1
PC0.Signal=GPIO_Output
PC1.Mode=RMII
PC1.Signal=ETH_MDC
PC10.GPIOParameters=GPIO_Label
PC10.GPIO_Label=GPIO_OUT5
PC10.Signal=GPIO_Output
PC11.Mode=Asynchronous
PC11.Signal=UART4_RX
PC12.Mode=SD_1_bit
PC12.Signal=SDMMC1_CK
PC13.GPIOParameters=GPIO_Label
PC13.GPIO_Label=USER_SWITCH1
PC13.Signal=GPIO_Input
PC14-OSC32_IN\ (OSC32_IN).Mode=LSE-External-Oscillator
PC14-OSC32_IN\ (OSC32_IN).Signal=RCC_OSC32_IN
PC15-OSC32_OUT\ (OSC32_OUT).Mode=LSE-External-Oscillator
PC15-OSC32_OUT\ (OSC32_OUT).Signal=RCC_OSC32_OUT
PC2_C.GPIOParameters=GPIO_Label
PC2_C.GPIO_Label=GPIO_OUT2
PC2_C.Signal=GPIO_Output
PC3_C.GPIOParameters=GPIO_Label
PC3_C.GPIO_Label=GPIO_OUT3
PC3_C.Signal=GPIO_Output
PC4.Mode=RMII
PC4.Signal=ETH_RXD0
PC5.Mode=RMII
PC5.Signal=ETH_RXD1
PC6.Mode=Asynchronous
PC6.Signal=USART6_TX
PC7.Mode=Asynchronous
PC7.Signal=USART6_RX
PC8.Mode=SD_1_bit
PC8.Signal=SDMMC1_D0
PC9.Mode=Single Bank 1
PC9.Signal=QUADSPI_BK1_IO0
PD0.Signal=FMC_D2_DA2
PD1.Signal=FMC_D3_DA3
PD10.Signal=FMC_D15_DA15
PD11.Signal=FMC_A16_CLE
PD12.Signal=FMC_A17_ALE
PD13.Signal=FMC_A18
PD14.Signal=FMC_D0_DA0
PD15.Signal=FMC_D1_DA1
PD2.Mode=SD_1_bit
PD2.Signal=SDMMC1_CMD
PD3.GPIOParameters=GPIO_Label
PD3.GPIO_Label=GPIO_OUT6
PD3.Signal=GPIO_Output
PD4.Signal=FMC_NOE
PD5.Signal=FMC_NWE
PD6.Signal=FMC_NWAIT
PD7.Mode=NorPsramChipSelect1_1
PD7.Signal=FMC_NE1
PD8.Signal=FMC_D13_DA13
PD9.Signal=FMC_D14_DA14
PE0.GPIOParameters=GPIO_Label
PE0.GPIO_Label=INT0_MVB
PE0.Signal=GPIO_Input
PE1.GPIOParameters=GPIO_Label
PE1.GPIO_Label=INT1_MVB
PE1.Signal=GPIO_Input
PE10.Signal=FMC_D7_DA7
PE11.Signal=FMC_D8_DA8
PE12.Signal=FMC_D9_DA9
PE13.Signal=FMC_D10_DA10
PE14.Signal=FMC_D11_DA11
PE15.Signal=FMC_D12_DA12
PE2.Mode=Single Bank 1
PE2.Signal=QUADSPI_BK1_IO2
PE3.GPIOParameters=GPIO_Label
PE3.GPIO_Label=RDY-MVB
PE3.Signal=GPIO_Input
PE4.GPIOParameters=GPIO_Label
PE4.GPIO_Label=RD-MVB
PE4.Signal=GPIO_Output
PE5.GPIOParameters=GPIO_Label
PE5.GPIO_Label=WR-MVB
PE5.Signal=GPIO_Output
PE6.GPIOParameters=GPIO_Label
PE6.GPIO_Label=TM_REQ_CPU-MVB
PE6.Signal=GPIO_Output
PE7.Signal=FMC_D4_DA4
PE8.Signal=FMC_D5_DA5
PE9.Signal=FMC_D6_DA6
PF0.Signal=FMC_A0
PF1.Signal=FMC_A1
PF10.GPIOParameters=GPIO_Label
PF10.GPIO_Label=DATA_ACK_MVB
PF10.Signal=GPIO_Input
PF11.GPIOParameters=GPIO_Label
PF11.GPIO_Label=STROBE_MVB
PF11.Signal=GPIO_Input
PF12.Signal=FMC_A6
PF13.Signal=FMC_A7
PF14.Signal=FMC_A8
PF15.Signal=FMC_A9
PF2.Signal=FMC_A2
PF3.Signal=FMC_A3
PF4.Signal=FMC_A4
PF5.Signal=FMC_A5
PF6.Mode=Single Bank 1
PF6.Signal=QUADSPI_BK1_IO3
PF7.Mode=Asynchronous
PF7.Signal=UART7_TX
PF8.Mode=Hardware Flow Control (RS485)
PF8.Signal=UART7_DE
PF9.Mode=Single Bank 1
PF9.Signal=QUADSPI_BK1_IO1
PG0.Signal=FMC_A10
PG1.Signal=FMC_A11
PG10.GPIOParameters=GPIO_Label
PG10.GPIO_Label=GPIO_ANALOG3
PG10.Signal=GPIO_Analog
PG11.Mode=RMII
PG11.Signal=ETH_TX_EN
PG12.GPIOParameters=GPIO_Label
PG12.GPIO_Label=LED_USART6
PG12.Signal=GPIO_Output
PG13.GPIOParameters=GPIO_Label
PG13.GPIO_Label=LED_UART4
PG13.Signal=GPIO_Output
PG14.GPIOParameters=GPIO_Label
PG14.GPIO_Label=LED_UART_7
PG14.Signal=GPIO_Output
PG15.GPIOParameters=GPIO_Label
PG15.GPIO_Label=LED_SD
PG15.Signal=GPIO_Output
PG2.Signal=FMC_A12
PG3.Signal=FMC_A13
PG4.Signal=FMC_A14_BA0
PG5.Signal=FMC_A15_BA1
PG6.Mode=Single Bank 1
PG6.Signal=QUADSPI_BK1_NCS
PG7.GPIOParameters=GPIO_Label
PG7.GPIO_Label=ERR_USB
PG7.Signal=GPIO_Input
PG8.Mode=Hardware Flow Control (RS485)
PG8.Signal=USART6_DE
PG9.GPIOParameters=GPIO_Label
PG9.GPIO_Label=ENABLE_USB
PG9.Signal=GPIO_Output
PH0-OSC_IN\ (PH0).Mode=HSE-External-Oscillator
PH0-OSC_IN\ (PH0).Signal=RCC_OSC_IN
PH1-OSC_OUT\ (PH1).Mode=HSE-External-Oscillator
PH1-OSC_OUT\ (PH1).Signal=RCC_OSC_OUT
RCC.SYSCLKFreq_VALUE=64000000
board=custom

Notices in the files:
parts and their libraries:
Copyright 2016 Accelerated Designs. All rights reserved.
